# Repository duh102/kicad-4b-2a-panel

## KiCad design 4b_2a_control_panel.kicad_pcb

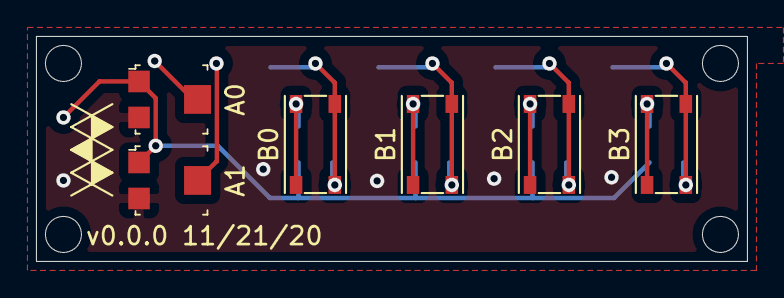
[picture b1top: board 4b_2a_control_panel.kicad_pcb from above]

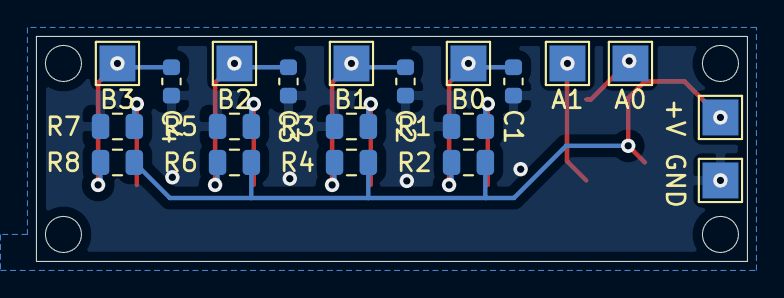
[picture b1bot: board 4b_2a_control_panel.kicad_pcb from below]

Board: 2 copper layers, 39.5 x 12.5 mm, 26 parts (20 on the bottom side), 12 nets.

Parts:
+V: TestPoint; TestPoint_Pad_2.0x2.0mm
A0, A1: TestPoint; TestPoint_Pad_2.0x2.0mm
A0#2, A1#2: TC33X-2-103E; Trimpot_3.8mmx3.6mm_TC33X-2-103E
B0, B1, B2, B3: TestPoint; TestPoint_Pad_2.0x2.0mm
B0#2, B1#2, B2#2, B3#2: SW_Push; SW_Push_1P1T_Vertical_CK_PTS815
C1, C2, C3, C4: 0.1pF; C_0603_1608Metric
GND: TestPoint; TestPoint_Pad_2.0x2.0mm
R1, R3, R5, R7: 1kR; R_0805_2012Metric
R2, R4, R6, R8: 10kR; R_0805_2012Metric

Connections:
+V: +V.1, A0#2.1, A1#2.1, R2.1, R4.1, R6.1, R8.1
A0: A0.1, A0#2.2
A1: A1.1, A1#2.2
B0: B0.1, B0#2.2, C1.1, R2.2
B1: B1.1, B1#2.2, C2.1, R4.2
B2: B2.1, B2#2.2, C3.1, R6.2
B3: B3.1, B3#2.2, C4.1, R8.2
GND: A0#2.3, A1#2.3, C1.2, C2.2, C3.2, C4.2, GND.1, R1.2, R3.2, R5.2, R7.2
unnamed: B0#2.1, R1.1
unnamed: B1#2.1, R3.1
unnamed: B2#2.1, R5.1
unnamed: B3#2.1, R7.1
